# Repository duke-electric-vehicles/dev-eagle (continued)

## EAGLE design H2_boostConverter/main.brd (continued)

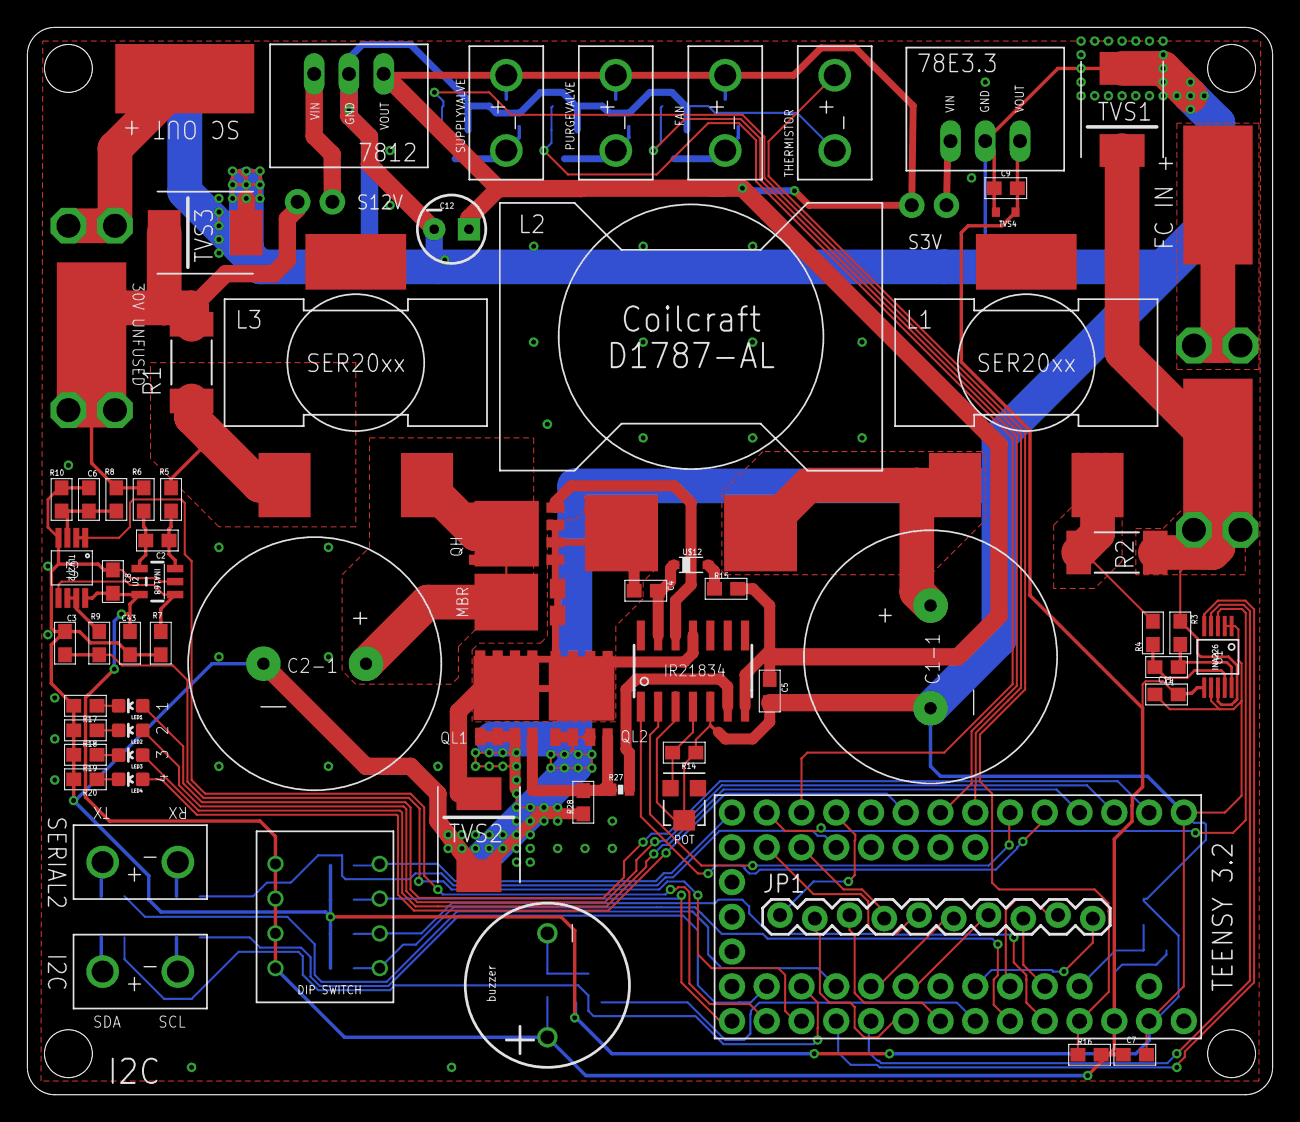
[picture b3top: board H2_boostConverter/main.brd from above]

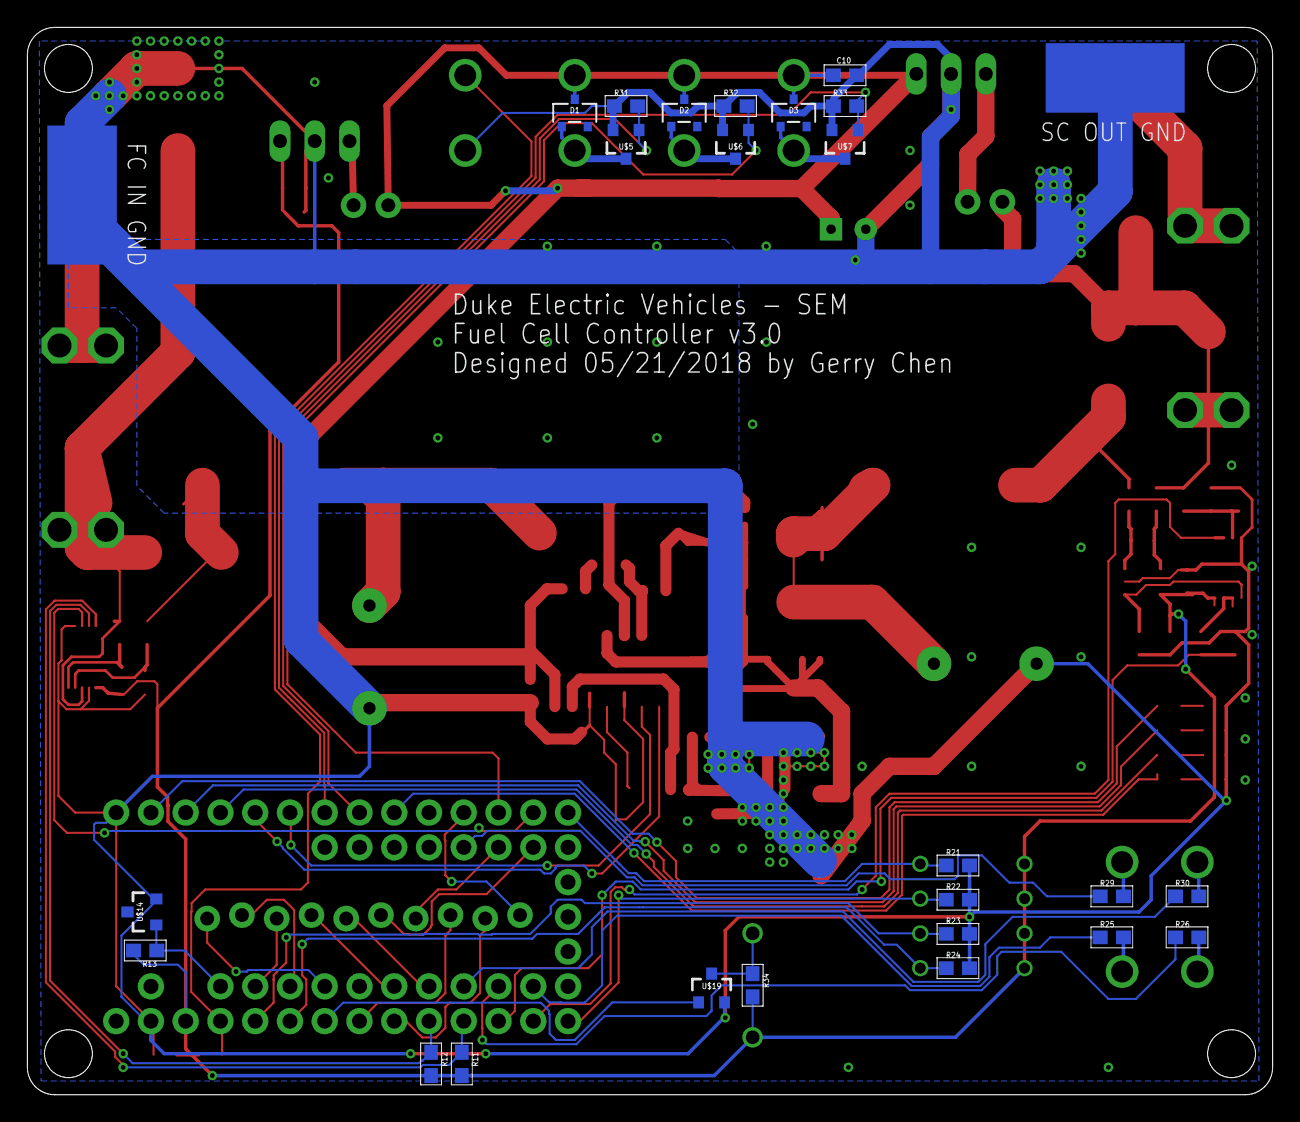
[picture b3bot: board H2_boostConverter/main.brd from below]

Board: 2 copper layers, 91.0 x 78.0 mm, 105 parts (26 on the bottom side), 74 nets.

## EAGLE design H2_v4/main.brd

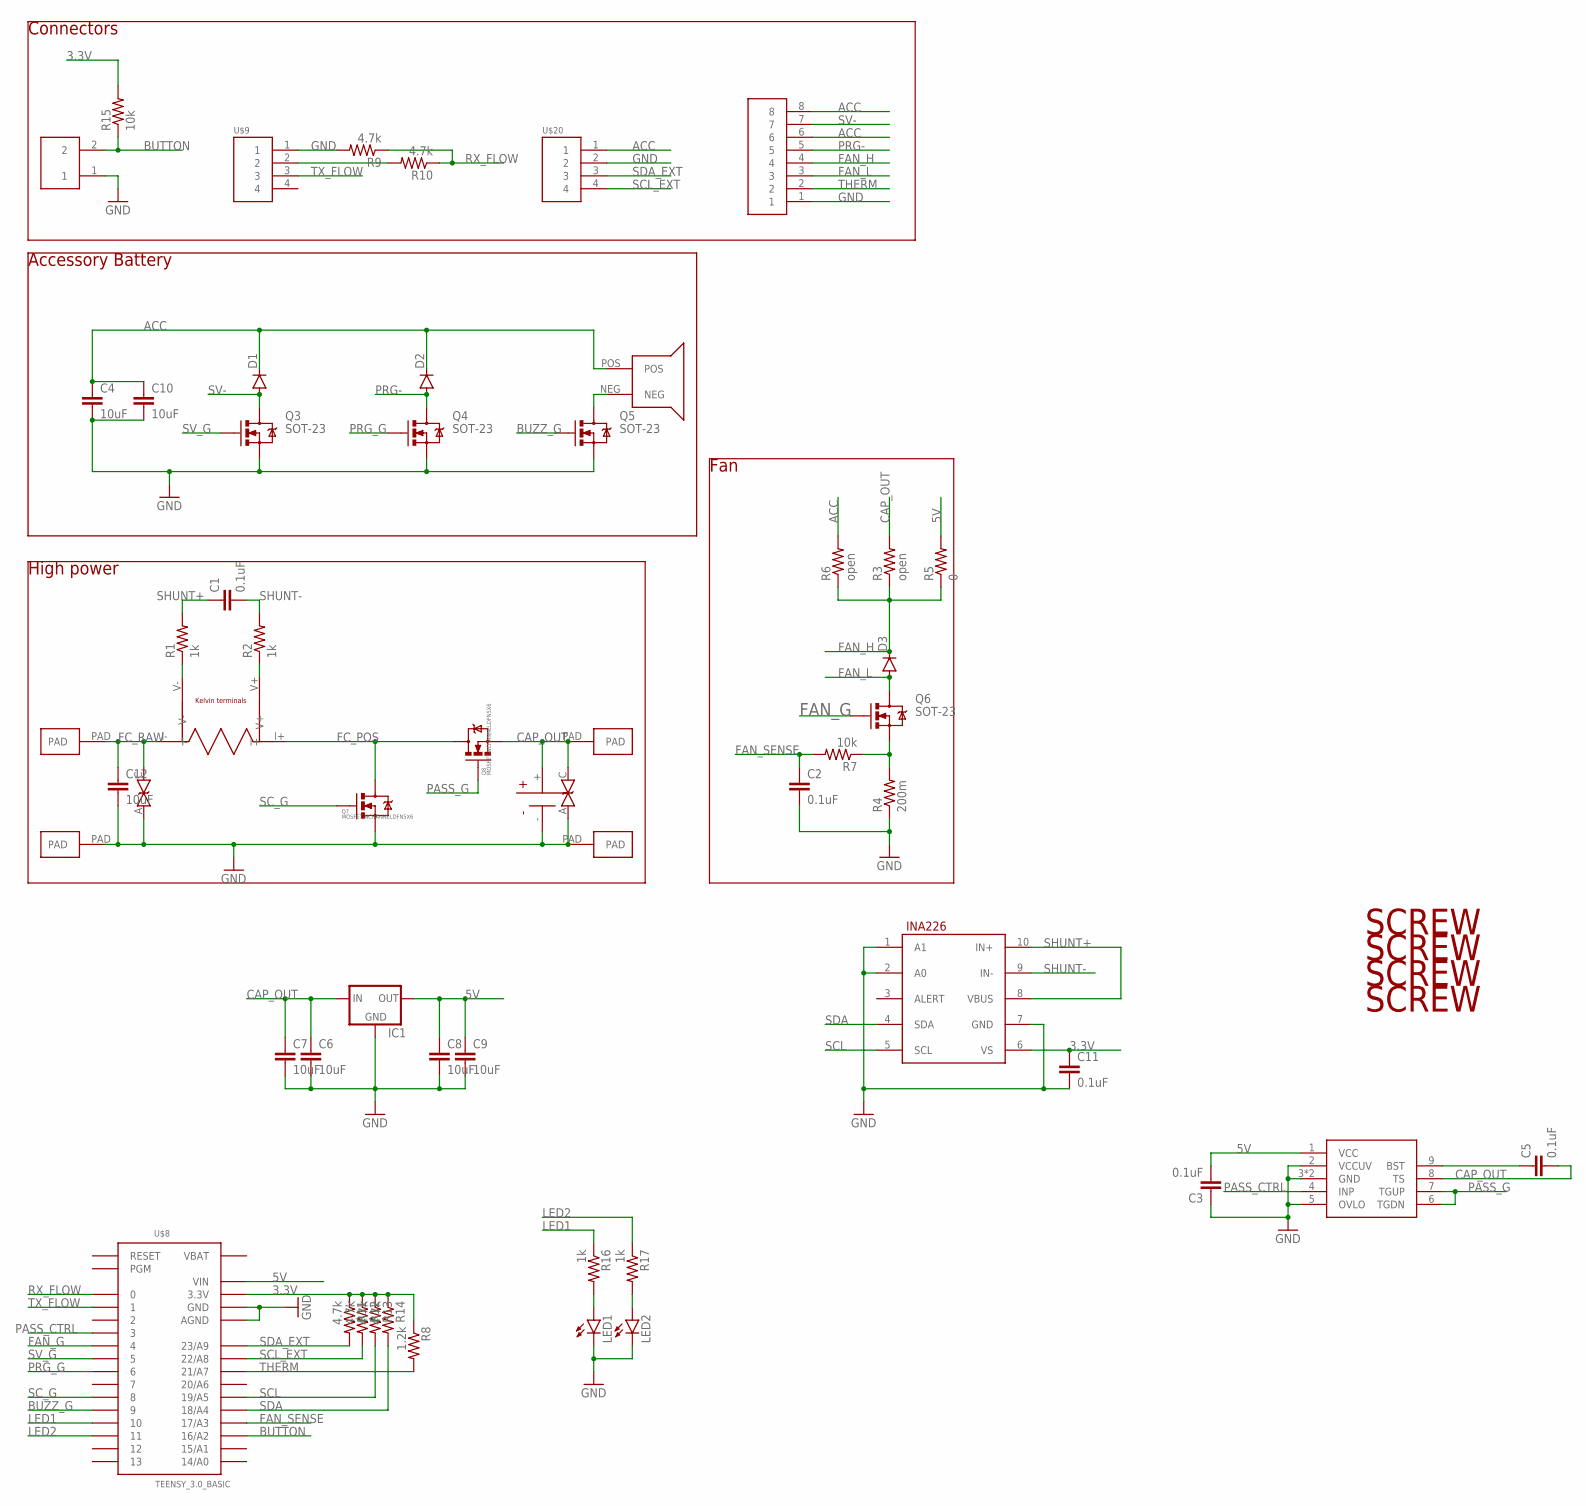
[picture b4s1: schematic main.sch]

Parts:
C1, C2, C3, C5, C11: 0.1uF; 0603-CAP
C4, C6, C7, C8, C9, C10, C12: 10uF; 1206
D1, D2, D3: DIODESOD123; SOD-123
IC1: V_REG_78XXV78W; V78W
LED1, LED2: LED1206; LED-1206
Q3, Q4, Q5, Q6: SOT-23; SOT23-3
Q7, Q8: MOSFET-NCHANNELDFN5X6; DFN5X6
R1, R2, R16, R17: 1k; 0603-RES
R3, R6: open; 0603-RES
R4: 200m; 0603-RES
R5: 0; 0603-RES
R7, R15: 10k; 0603-RES
R8: 1.2k; 0603-RES
R9, R10, R11, R12, R13, R14: 4.7k; 0603-RES
U$1: SHUNT_KELVIN; 2512_KELVIN
U$2: INA226; PSOP-10
U$3, U$4, U$10, U$11: PAD
U$5: HEADER8; 8PINVALULOK
U$6: LTC7001; PSOP-10-EP
U$7: BUZZER12MM; BUZZER_12MM
U$8: TEENSY_3.0_BASIC
U$9, U$20: HEADER4VALULOK; 4PINVALULOK
U$12: CAP-AL_ELECTROLYTIC; CAP-RADIAL
U$13: HEADER2; 2PINVALULOK
U$14, U$15, U$18, U$19: SCREW; M3HOLE
U$16, U$17: TVS_BIDO-214AB; DO-214AB

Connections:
3.3V: C11.1, R8.1, R11.1, R12.1, R13.1, R14.1, R15.2, U$2.6 (VS), U$8.3.3V, U$8.3.3V1 (3.3V)
5V: C3.2, C8.1, C9.1, IC1.OUT, R5.2, U$6.1 (VCC), U$8.VIN
ACC: C4.1, C10.1, D1.C, D2.C, R6.2, U$5.6, U$5.8, U$7.POS, U$20.1
BUTTON: R15.1, U$8.16/A2, U$13.2
BUZZ_G: Q5.1 (G), U$8.9
CAP_OUT: C5.2, C6.1, C7.1, IC1.IN, Q8.1 (S), Q8.2 (S), Q8.3 (S), R3.2, U$6.8 (TS), U$10.PAD, U$12.+ (V+), U$17.C (2)
FAN_G: Q6.1 (G), U$8.4
FAN_H: D3.C, R3.1, R5.1, R6.1, U$5.4
FAN_L: D3.A, Q6.3 (D), U$5.3
FAN_SENSE: C2.1, R7.2, U$8.17/A3
FC_POS: Q7.PAD (D), Q8.PAD (D), U$1.I+
FC_RAW: C12.1, U$1.I-, U$3.PAD, U$16.C (2)
GND: C2.2, C3.1, C4.2, C6.2, C7.2, C8.2, C9.2, C10.2, C11.2, C12.2, IC1.GND, LED1.C, LED2.C, Q3.2 (S), Q4.2 (S), Q5.2 (S), Q7.1 (S), Q7.2 (S), Q7.3 (S), R4.1, R9.2, U$2.1 (A1), U$2.2 (A0), U$2.7 (GND), U$4.PAD, U$5.1, U$6.2 (VCCUV), U$6.3 (GND), U$6.5 (OVLO), U$6.PAD (GND), U$8.AGND, U$8.GND, U$8.GND1 (GND), U$9.1, U$11.PAD, U$12.- (V-), U$13.1, U$16.A (1), U$17.A (1), U$20.2
LED1: R16.1, U$8.10
LED2: R17.1, U$8.11
unnamed: C5.1, U$6.9 (BST)
unnamed: LED1.A, R16.2
unnamed: Q5.3 (D), U$7.NEG
unnamed: R1.1, U$1.V-
unnamed: R2.1, U$1.V+
unnamed: Q6.2 (S), R4.2, R7.1
unnamed: R10.2, U$9.2
unnamed: LED2.A, R17.2
PASS_CTRL: U$6.4 (INP), U$8.3
PASS_G: Q8.4 (G), U$6.6 (TGDN), U$6.7 (TGUP)
PRG-: D2.A, Q4.3 (D), U$5.5
PRG_G: Q4.1 (G), U$8.6
RX_FLOW: R9.1, R10.1, U$8.0
SCL: R13.2, U$2.5 (SCL), U$8.19/A5
SCL_EXT: R12.2, U$8.22/A8, U$20.4
SC_G: Q7.4 (G), U$8.8
SDA: R14.2, U$2.4 (SDA), U$8.18/A4
SDA_EXT: R11.2, U$8.23/A9, U$20.3
SHUNT+: C1.1, R1.2, U$2.8 (VBUS), U$2.10 (IN+)
SHUNT-: C1.2, R2.2, U$2.9 (IN-)
SV-: D1.A, Q3.3 (D), U$5.7
SV_G: Q3.1 (G), U$8.5
THERM: R8.2, U$5.2, U$8.21/A7
TX_FLOW: U$8.1, U$9.3
VBAT: U$8.VBAT

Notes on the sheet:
Accessory Battery
High power
Fan
Connectors

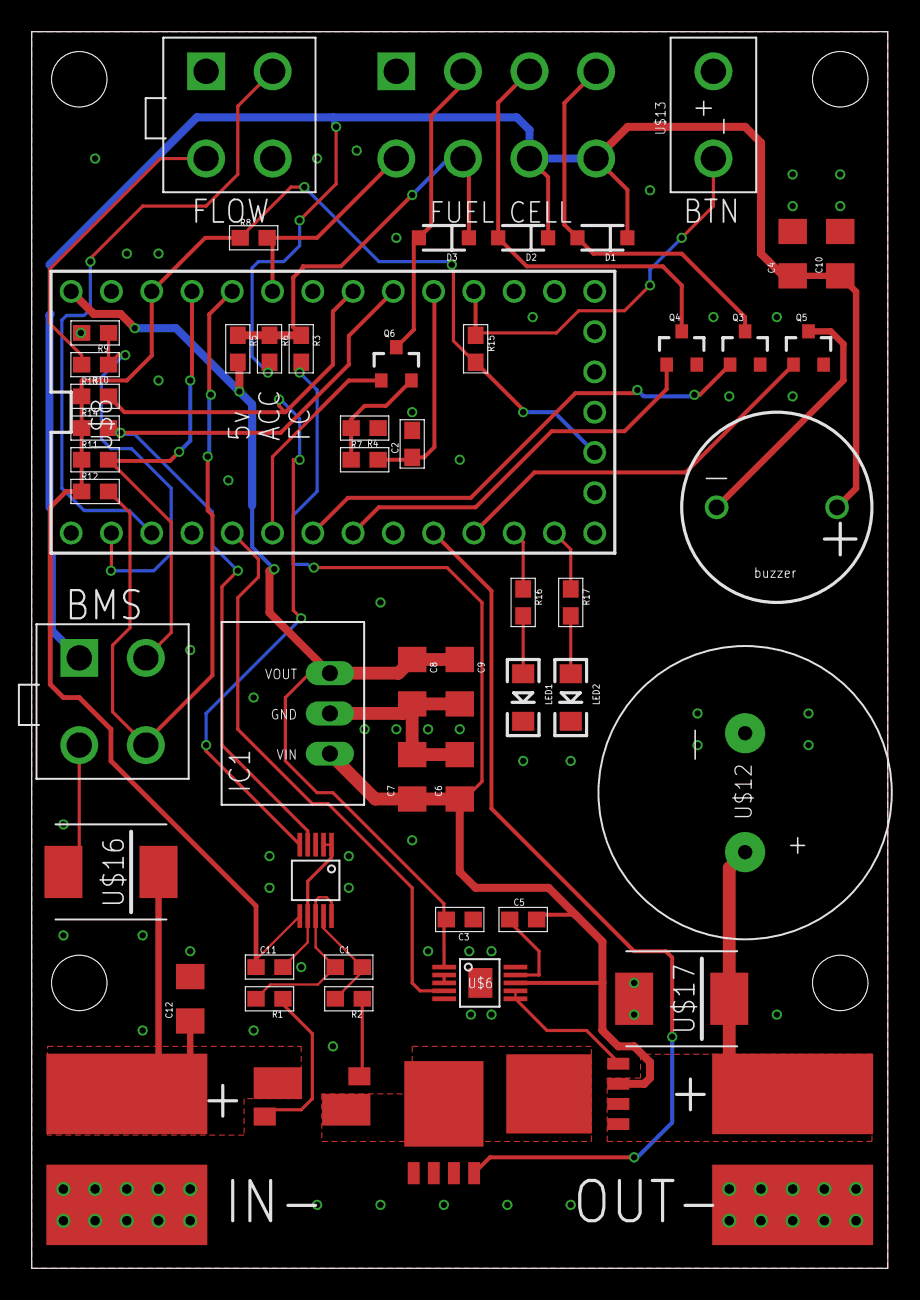
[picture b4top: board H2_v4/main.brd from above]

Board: 2 copper layers, 54.0 x 78.0 mm, 61 parts (0 on the bottom side), 39 nets.

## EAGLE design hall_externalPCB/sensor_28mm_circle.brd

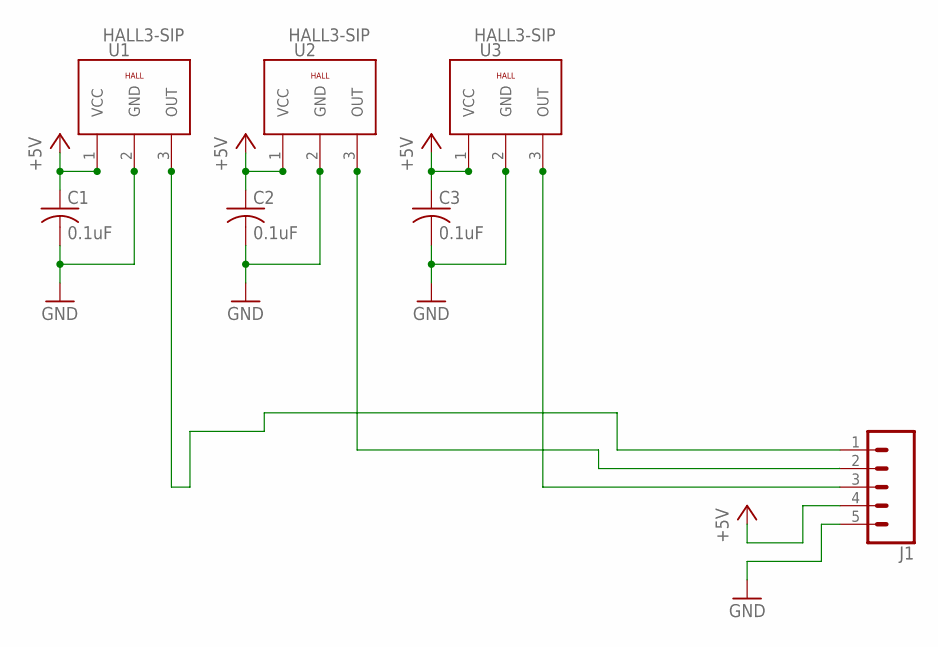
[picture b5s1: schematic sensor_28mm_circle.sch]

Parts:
C1, C2, C3: 0.1uF; C0603
J1: CONN_05PTH_LONGPADS; 1X05_LONGPADS
U1, U2, U3: HALL3-SIP; 3PINS1,27

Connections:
+5V: C1.1, C2.1, C3.1, J1.4, U1.1 (VCC), U2.1 (VCC), U3.1 (VCC)
GND: C1.2, C2.2, C3.2, J1.5, U1.2 (GND), U2.2 (GND), U3.2 (GND)
unnamed: J1.1, U1.3 (OUT)
unnamed: J1.3, U3.3 (OUT)
unnamed: J1.2, U2.3 (OUT)

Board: 2 copper layers, 7 parts (0 on the bottom side), 5 nets, no tracks yet.
